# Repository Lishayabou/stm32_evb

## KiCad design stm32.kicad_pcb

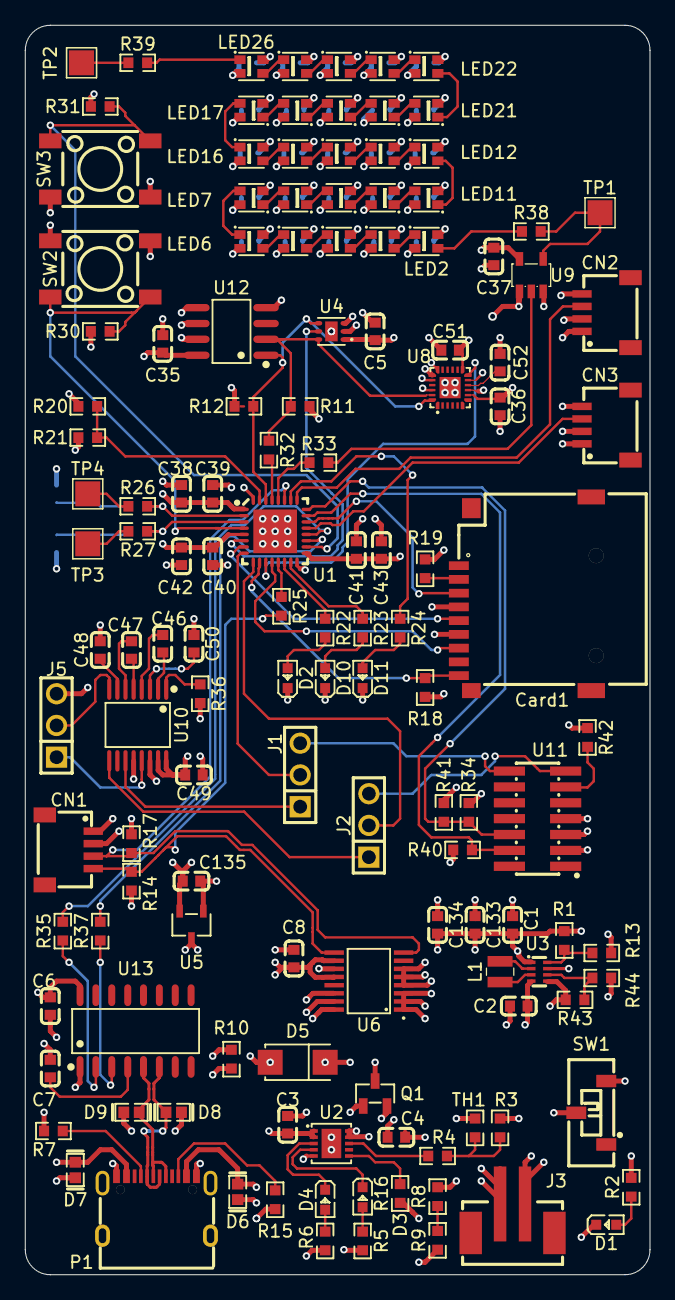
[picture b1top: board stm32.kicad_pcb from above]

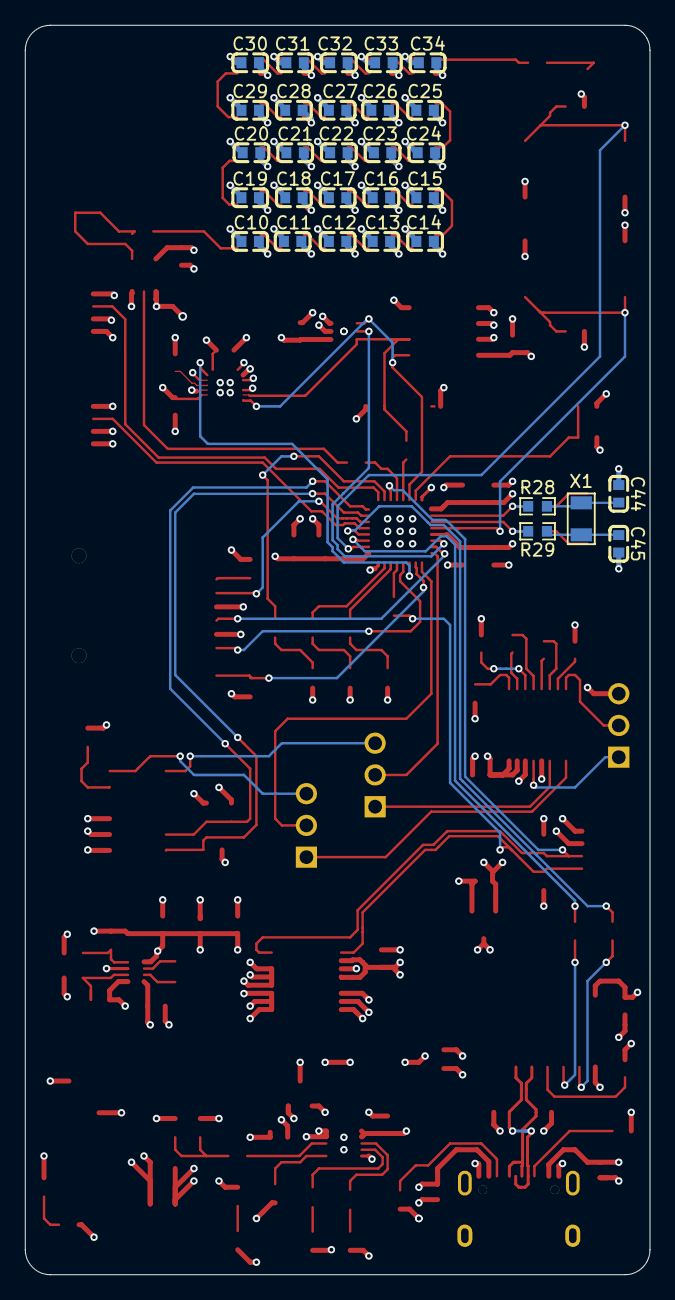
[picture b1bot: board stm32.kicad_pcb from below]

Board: 4 copper layers, 50.0 x 100.0 mm, 166 parts (30 on the bottom side), 109 nets.

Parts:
C1, C2, C3, C133, C135: CL10A106KP8NNNC; C0603
C4: CL10A226MP8NUNE; C0603
C5, C6, C7, C8, C10, C11, C12, C13, C14, C15, C16, C17, C18, C19, C20, C21, C22, C23, C24, C25, C26, C27, C28, C29, C30, C31, C32, C33, C34, C35, C36, C37, C39, C40, C41, C46, C47, C48, C49, C50, C51, C52: CC0603KRX7R9BB104; C0603
C38: CL10A475KO8NNNC; C0603
C42, C43: CL10A105KB8NNNC; C0603
C44, C45: 0603CG7R0C500NT; C0603
C134: CL10A225KO8NNNC; C0603
CN1, CN2, CN3: SM04B-SRSS-TB (LF)(SN); CONN-SMD_4P-P1.00_SM04B-SRSS-TB-LF-SN
Card1: TF PUSH; TF-SMD_TF-PUSH
D1, D2, D3: 0603 Green 509-620mcd; LED0603-RD
D4, D10, D11: KT-0603R; LED0603-RD
D5: MBRA210LT3G_C5337989; SMA_L4.3-W2.6-LS5.1-RD
D6, D7, D8, D9: 0603ESDA-05N; D0603-BI
J1, J2, J5: PZ254V-11-03P_C2937625; HDR-TH_3P-P2.54-V-M
J3: B2B-PH-SM4-TB (LF)(SN); CONN-SMD_B2B-PH-SM4-TB-LF-SN
L1: FTC252012S1R0MBCA; IND-SMD_L2.5-W2.0-VLS252012CX-150M
LED2, LED3, LED4, LED5, LED6, LED7, LED8, LED9, LED10, LED11, LED12, LED13, LED14, LED15, LED16, LED17, LED18, LED19, LED20, LED21, LED22, LED23, LED24, LED25, LED26: WS2812B-2020; LED-SMD_4P-L2.0-W2.0-TL_WS2812B-2020
P1: TYPE-C 16PIN 2MD(073); USB-C-SMD_TYPE-C-6PIN-2MD-073
Q1: DMG2301L-7; SOT-23-3_L2.9-W1.3-P1.90-LS2.4-BR
R1: 0603WAF8060T5E; R0603
R2, R5, R6: 0603WAF3300T5E; R0603
R3: 0603WAF7502T5E; R0603
R4: 0603WAF1431T5E; R0603
R7, R15, R16: 0603WAF5101T5E; R0603
R8, R9, R11, R12, R14, R17, R18, R19, R21, R30, R31, R36, R43, R44: 0603WAF1002T5E; R0603
R10: 0603WAF1003T5E; R0603
R13: 0603WAF910JT5E; R0603
R20, R34, R40: 0603WAF4701T5E; R0603
R22, R23, R24, R42: 0603WAF1000T5E; R0603
R25, R32, R33: 0603WAF220JT5E; R0603
R26, R27, R28, R29: 0603WAF0000T5E; R0603
R35, R37, R38, R39: 0603WAF4700T5E; R0603
R41: 0603WAF1001T5E; R0603
SW1: JS102011JCQN; SW-SMD_JS102011JCQN
SW2, SW3: 6.0*6.0*6.0; SW-SMD_4P-L6.0-W6.0-P4.50-LS8.6
TH1: NCP18XH103F03RB; R0603
TP1, TP2, TP3, TP4: TestPoint; TestPoint_Pad_2.0x2.0mm
U1: STM32L431KBU6_C2826408; QFN-32_L5.0-W5.0-P0.50-TL-EP3.5
U2: MCP73833T-AMI/MF; DFN-10_L3.0-W3.0-P0.50-BL-EP-1
U3: TPS631000DRLR; SOT-583-8_L2.1-W1.2-P0.50-LS1.6-BL
U4: OPT3004DNPR; WSON-6_L2.0-W2.0-P0.65-TL-EP
U5: XC6206P332MR_C347376; SOT-23-3_L3.0-W1.7-P0.95-LS2.9-BR
U6: INA260AIPWR; TSSOP-16_L5.0-W4.4-P0.65-LS6.4-BL-1
U8: MPU6500; QFN-24_L3.0-W3.0-P0.40-BL-EP
U9: SN74AHCT1G125DBVR; SOT-23-5_L3.0-W1.7-P0.95-LS2.8-BR
U10: MAX3221ECPWR; TSSOP-16_L5.0-W4.4-P0.65-LS6.4-BL
U11: HB-PH9-12727PB2GOB; HDR-SMD_14P-P1.27-V-M-R2-C7-LS5.5
U12: TMP75AIDR; SOIC-8_L4.9-W3.9-P1.27-LS6.0-BL
U13: CH340C_C7464026; SOP-16_L10.0-W3.9-P1.27-LS6.0-BL
X1: SC-32S32.768kHz20PPM7pF; OSC-SMD_L3.2-W1.5

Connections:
+3V3: C5.2, C35.2, C36.2, C38.1, C39.1, C40.1, C41.1, C42.1, C43.1, C49.2, C51.2, C135.2, CN1.2, CN2.2, CN3.2, Card1.4 (VDD), R11.2, R12.2, R14.2, R17.2, R18.2, R19.2, R20.1, R30.2, R31.2, R34.1, R40.1, U1.1 (VDD), U1.5 (VDDA/VREF+), U1.17 (VDD), U4.1 (VDD), U5.2 (VOUT), U8.8 (VDDIO), U8.13 (VDD), U8.22 (nCS), U10.12 (FORCEON), U10.15 (VCC), U10.16 (~FORCEOFF), U11.3, U12.8 (V+)
+5V: C10.2, C11.2, C12.2, C13.2, C14.2, C15.2, C16.2, C17.2, C18.2, C19.2, C20.2, C21.2, C22.2, C23.2, C24.2, C25.2, C26.2, C27.2, C28.2, C29.2, C30.2, C31.2, C32.2, C33.2, C34.2, C37.2, LED2.4 (VDD), LED3.4 (VDD), LED4.4 (VDD), LED5.4 (VDD), LED6.4 (VDD), LED7.4 (VDD), LED8.4 (VDD), LED9.4 (VDD), LED10.4 (VDD), LED11.4 (VDD), LED12.4 (VDD), LED13.4 (VDD), LED14.4 (VDD), LED15.4 (VDD), LED16.4 (VDD), LED17.4 (VDD), LED18.4 (VDD), LED19.4 (VDD), LED20.4 (VDD), LED21.4 (VDD), LED22.4 (VDD), LED23.4 (VDD), LED24.4 (VDD), LED25.4 (VDD), LED26.4 (VDD), U5.3 (VIN), U6.14 (IN-), U6.15 (IN-), U6.16 (IN-), U9.5 (VCC)
+5VP: C3.2, C6.2, D5.2 (A), D6.2, D7.2, P1.2 (VBUS), P1.11 (VBUS), Q1.1 (G), R5.2, R6.2, R10.2, U2.1 (VDD), U2.2 (VDD), U13.16 (VCC)
/USB/5V_INA: C1.2, C8.2, C133.2, C134.2, R1.2, U3.1 (VOUT), U6.1 (IN+), U6.2 (IN+), U6.3 (IN+), U6.10 (VS), U6.12 (VBUS)
/USB/CC1: P1.4 (CC1), R7.2
/USB/CC2: P1.10 (CC2), R15.2
/USB/P_MODE: R43.1, R44.2, U3.6 (MODE)
/USB/RXD_0: R35.1, U1.20 (PA10)
/USB/STAT1: D4.1 (K), U2.3 (STAT1)
/USB/STAT2: D3.1 (K), U2.4 (STAT2)
/USB/TXD_0: R37.1, U1.19 (PA9)
/USB/USB_D+: D9.2, P1.6 (DP1), P1.8 (DP2), U13.5 (UD+)
/USB/USB_D-: D8.2, P1.5 (DN2), P1.7 (DN1), U13.6 (UD-)
/USB/USB_RX: R37.2, U13.3 (RXD)
/USB/USB_TX: R35.2, U13.2 (TXD)
/USB/VIN: C2.2, R2.2, R43.2, SW1.3, U3.4 (VIN), U3.5 (EN)
/USB/raw_voltage: D5.1 (C), Q1.3 (D), SW1.2
/sensors/SCL: R11.1, R32.2, U4.6 (SDA), U8.23 (SCL/SCLK), U12.2 (SCL)
/sensors/SDA: R12.1, U1.30 (PB7), U4.4 (SCL), U8.24 (SDA/SDI), U12.1 (SDA)
/sensors/SPI_CS: Card1.2 (CD/DAT3), R19.1
/sensors/led_matrix/DIN: R38.1, TP1.1, U9.4 (Y)
/sensors/led_matrix/DOUT: R39.1, TP2.1
/stm32_page/BOOT0: R20.2, R21.2, U1.31 (PH3/BOOT0)
/stm32_page/I2C1_SCL_R: R32.1, U1.29 (PB6)
/stm32_page/I2C3_SCL: CN1.4, R14.1, R25.1, U6.9 (SCL)
/stm32_page/I2C3_SCL_R: R25.2, U1.13 (PA7)
/stm32_page/I2C3_SDA: CN1.3, R17.1, U1.27 (PB4), U6.8 (SDA)
/stm32_page/IMU_INT: U1.11 (PA5), U8.12 (INT)
/stm32_page/LED1: R22.2, U1.14 (PB0)
/stm32_page/LED2: R23.2, U1.15 (PB1)
/stm32_page/LED3: R24.2, U1.26 (PB3)
/stm32_page/MAX3221_RX_OUT: J2.1, U10.9 (ROUT)
/stm32_page/MAX3221_TX_IN: J1.1, U10.11 (DIN)
/stm32_page/OSC32_IN: C44.2, R28.1, X1.1
/stm32_page/OSC32_OUT: C45.2, R29.1, X1.2
/stm32_page/PB_SW1: R31.1, SW3.1, SW3.2, U1.18 (PA8)
/stm32_page/PWM_CH1: CN2.3, U1.25 (PA15)
/stm32_page/PWM_CH4: CN3.3, U1.21 (PA11)
/stm32_page/RGB_LEDS: R33.2, U9.2 (A)
/stm32_page/RGB_LEDS_R: R33.1, U1.28 (PB5)
/stm32_page/SD_CD: Card1.9 (CD), R18.1, U1.10 (PA4)
/stm32_page/SPI1_MISO: Card1.7 (DAT0), U1.12 (PA6)
/stm32_page/SPI1_MOSI: Card1.3 (CMD), U1.22 (PA12)
/stm32_page/SPI1_SCK: Card1.5 (CLX), U1.7 (PA1)
/stm32_page/STM32_NRST: R30.1, SW2.1, SW2.2, U1.4 (NRST)
/stm32_page/SWCLK: R34.2, R41.1, U1.24 (PA14), U11.6
/stm32_page/SWDIO: R40.2, U1.23 (PA13), U11.4
/stm32_page/SYS_WKUP1: U1.6 (PA0/CK_IN), U4.5 (INT)
/stm32_page/UART2_RX: J2.2, U1.9 (PA3)
/stm32_page/UART2_RX_CONN: J5.2, U10.8 (RIN)
/stm32_page/UART2_TX: J1.2, U1.8 (PA2)
/stm32_page/UART2_TX_CONN: J5.1, U10.13 (DOUT)
/stm32_page/VCP_RX: J2.3, U11.13
/stm32_page/VCP_TX: J1.3, U11.14
GND: C1.1, C2.1, C3.1, C4.1, C5.1, C6.1, C7.1, C8.1, C10.1, C11.1, C12.1, C13.1, C14.1, C15.1, C16.1, C17.1, C18.1, C19.1, C20.1, C21.1, C22.1, C23.1, C24.1, C25.1, C26.1, C27.1, C28.1, C29.1, C30.1, C31.1, C32.1, C33.1, C34.1, C35.1, C36.1, C37.1, C38.2, C39.2, C40.2, C41.2, C42.2, C43.2, C44.1, C45.1, C48.2, C49.1, C50.2, C51.1, C52.1, C133.1, C134.1, C135.1, CN1.1, CN2.1, CN2.4, CN3.1, CN3.4, Card1.6 (VSS), D1.1 (K), D2.1 (K), D6.1, D7.1, D8.1, D9.1, D10.1 (K), D11.1 (K), J3.1, J5.3, LED2.2 (GND), LED3.2 (GND), LED4.2 (GND), LED5.2 (GND), LED6.2 (GND), LED7.2 (GND), LED8.2 (GND), LED9.2 (GND), LED10.2 (GND), LED11.2 (GND), LED12.2 (GND), LED13.2 (GND), LED14.2 (GND), LED15.2 (GND), LED16.2 (GND), LED17.2 (GND), LED18.2 (GND), LED19.2 (GND), LED20.2 (GND), LED21.2 (GND), LED22.2 (GND), LED23.2 (GND), LED24.2 (GND), LED25.2 (GND), LED26.2 (GND), P1.1 (GND), P1.12 (GND), P1.13 (SHELL), P1.14 (SHELL), R3.1, R7.1, R9.1, R10.1, R13.1, R15.1, R16.1, R21.1, R36.2, R41.2, R42.2, R44.1, SW2.3, SW2.4, SW3.3, SW3.4, TH1.2, U1.16 (VSS), U1.32 (VSS), U1.33 (EP), U2.5 (VSS), U2.11 (EP), U3.7 (GND), U4.2 (ADDR), U4.3 (GND), U4.7 (EP), U5.1 (VSS), U6.4 (A1), U6.5 (A0), U6.6 (GND), U6.11 (GND), U8.9 (SDO/AD0), U8.11 (FSYNC), U8.18 (GND), U8.19 (RESV), U8.20 (RESV), U8.25 (EP), U9.1 (~OE), U9.3 (GND), U10.14 (GND), U11.5, U11.7, U12.4 (GND), U12.5 (A2), U12.6 (A1), U12.7 (A0), U13.1 (GND)
LIPO+: C4.2, J3.2, Q1.2 (S), R8.2, U2.9 (VBAT), U2.10 (VBAT)
unnamed: D1.2 (A), R2.1
unnamed: D2.2 (A), R22.1
unnamed: D3.2 (A), R5.1
unnamed: D4.2 (A), R6.1
unnamed: D10.2 (A), R23.1
unnamed: D11.2 (A), R24.1
unnamed: LED2.3 (DI), R38.2
unnamed: LED2.1 (DO), LED3.3 (DI)
unnamed: LED3.1 (DO), LED4.3 (DI)
unnamed: LED4.1 (DO), LED5.3 (DI)
unnamed: LED5.1 (DO), LED6.3 (DI)
unnamed: LED6.1 (DO), LED7.3 (DI)
unnamed: LED7.1 (DO), LED8.3 (DI)
unnamed: LED8.1 (DO), LED9.3 (DI)
unnamed: LED9.1 (DO), LED10.3 (DI)
unnamed: LED10.1 (DO), LED11.3 (DI)
unnamed: LED11.1 (DO), LED12.3 (DI)
unnamed: LED12.1 (DO), LED13.3 (DI)
unnamed: LED13.1 (DO), LED14.3 (DI)
unnamed: LED14.1 (DO), LED15.3 (DI)
unnamed: LED15.1 (DO), LED16.3 (DI)
unnamed: LED16.1 (DO), LED17.3 (DI)
unnamed: LED17.1 (DO), LED18.3 (DI)
unnamed: LED18.1 (DO), LED19.3 (DI)
unnamed: LED19.1 (DO), LED20.3 (DI)
unnamed: LED20.1 (DO), LED21.3 (DI)
unnamed: LED21.1 (DO), LED22.3 (DI)
unnamed: LED22.1 (DO), LED23.3 (DI)
unnamed: LED23.1 (DO), LED24.3 (DI)
unnamed: LED24.1 (DO), LED25.3 (DI)
unnamed: LED25.1 (DO), LED26.3 (DI)
unnamed: LED26.1 (DO), R39.2
unnamed: R3.2, R4.2, TH1.1
unnamed: R8.1, R9.2
unnamed: R26.1, TP4.1
unnamed: R27.1, TP3.1
unnamed: R42.1, U11.11
unnamed: R26.2, R28.2, U1.2 (PC14-OSC32_IN)
unnamed: R27.2, R29.2, U1.3 (PC15-OSC32_OUT)
unnamed: R16.2, U2.6 (PROG)
unnamed: R4.1, U2.8 (THERM)
unnamed: R1.1, R13.2, U3.8 (FB)
unnamed: L1.1, U3.3 (LX1)
unnamed: L1.2, U3.2 (LX2)
unnamed: C52.2, U8.10 (REGOUT)
unnamed: C46.1, U10.2 (C1+)
unnamed: C46.2, U10.4 (C1-)
unnamed: C47.1, U10.5 (C2+)
unnamed: C47.2, U10.6 (C2-)
unnamed: C50.1, U10.3 (V+)
unnamed: C48.1, U10.7 (V-)
unnamed: R36.1, U10.1 (~EN)
unnamed: C7.2, U13.4 (V3)

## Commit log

2025-04-07 pre placement and type c routing
2025-04-07 routing - type c and all 5vp+ cmp
2025-04-07 routing all power
2025-04-10 all done except rgb leds and i2c sns
2025-04-10 all done except rgb leds (to finish) and i2c sns
2025-04-20 RGB leds done
2025-04-21 i2c sns done - all done
2025-04-21 fix DRC except via size to all
2025-04-21 final board - I change the min annular width from 0.2 to 0.15 instead of replacing all vias. but for JLC 0.2mm is prefered
